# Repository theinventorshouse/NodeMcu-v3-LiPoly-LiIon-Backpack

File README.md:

# NodeMCU DEVKIT V1.0 LiPoly LiIon Backpack
ESP8266 NodeMCU DEVKIT V1.0 (or Node Mcu V3) LiPoly/LiIon Backpack

The Inventor's House invests time and resources providing this open source code,
please support The Inventor's House and open-source hardware by purchasing
products from The Inventor's House!

Designed by The Inventor's House.
CERN Open Hardware Licence 1.2 (CERN OHL 1.2), check cern_ohl_v_1_2.txt for more information All text above must be included in any redistribution

Order the pc board from SeedStudio and assemble your own or order the fully assembled and tested LiPo charger from me and see what fast LiPo battery charging can do for your application!

Use Library Kicad
____________

https://github.com/sabas1080/kicadlibrary

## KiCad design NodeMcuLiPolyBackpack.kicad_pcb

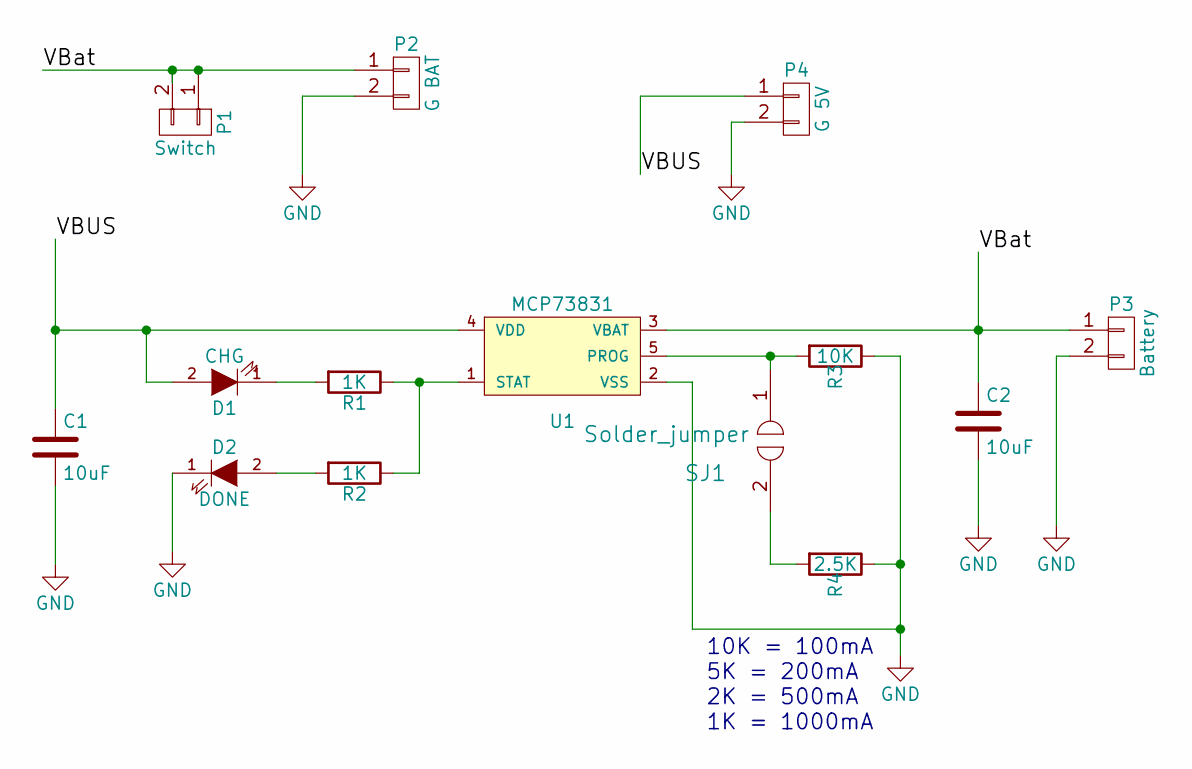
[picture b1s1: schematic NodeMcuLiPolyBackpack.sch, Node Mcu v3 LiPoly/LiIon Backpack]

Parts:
C1, C2: 10uF; C_0603_HandSoldering
D1: CHG; LED-0603
D2: DONE; LED-0603
P1: Switch; Pin_Header_Straight_1x02
P2: G BAT; Pin_Header_Straight_1x02
P3: Battery; CONN_JST-2_SMD
P4: G 5V; Pin_Header_Straight_1x02
R1, R2: 1K; R_0603_HandSoldering
R3: 10K; R_0603_HandSoldering
R4: 2.5K; R_0603_HandSoldering
SJ1: Solder_jumper; S_JUMPER_2
U1: MCP73831; SOT-23-5

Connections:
/VBUS: C1.1, D1.2 (A), P4.1, U1.4 (VDD)
/VBat: C2.1, P1.1, P1.2, P2.1, P3.1, U1.3 (VBAT)
GND: C1.2, C2.2, D2.1 (K), P2.2, P3.2, P4.2, R3.1, R4.1, U1.2 (VSS)
unnamed: D1.1 (K), R1.2
unnamed: D2.2 (A), R2.2
unnamed: R1.1, R2.1, U1.1 (STAT)
unnamed: R3.2, SJ1.1, U1.5 (PROG)
unnamed: R4.2, SJ1.2

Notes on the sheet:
10K = 100mA 5K = 200mA 2K = 500mA 1K = 1000mA

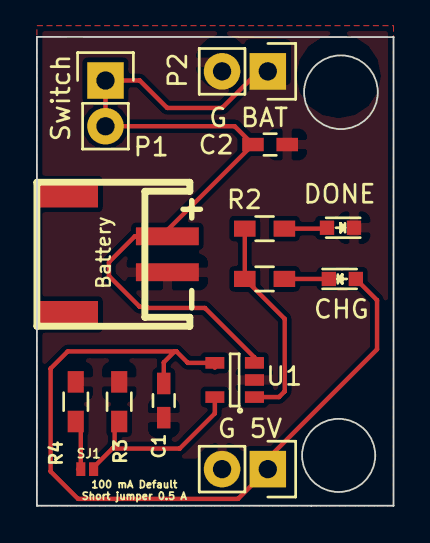
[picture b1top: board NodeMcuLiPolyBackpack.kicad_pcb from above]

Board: 2 copper layers, 19.8 x 26.0 mm, 15 parts (1 on the bottom side), 8 nets.

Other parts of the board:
LOGO: LOGO

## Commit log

2015-11-02 Primer commit, esquematico listo
2015-11-03 Update Fix Jumper
2015-11-03 Fix connector, add PCB
2015-11-10 Ruteo
2015-11-11 Agregados medidas de orificios y pines.
2015-11-11 Revision de Medidas de pines
2015-11-11 Logo, reacomodo v1.0
2015-11-11 Fix autosave
2015-11-11 Fix F-slinks
2015-12-01 Update Documents
2015-12-28 Fix size
2016-01-06 Fixes
